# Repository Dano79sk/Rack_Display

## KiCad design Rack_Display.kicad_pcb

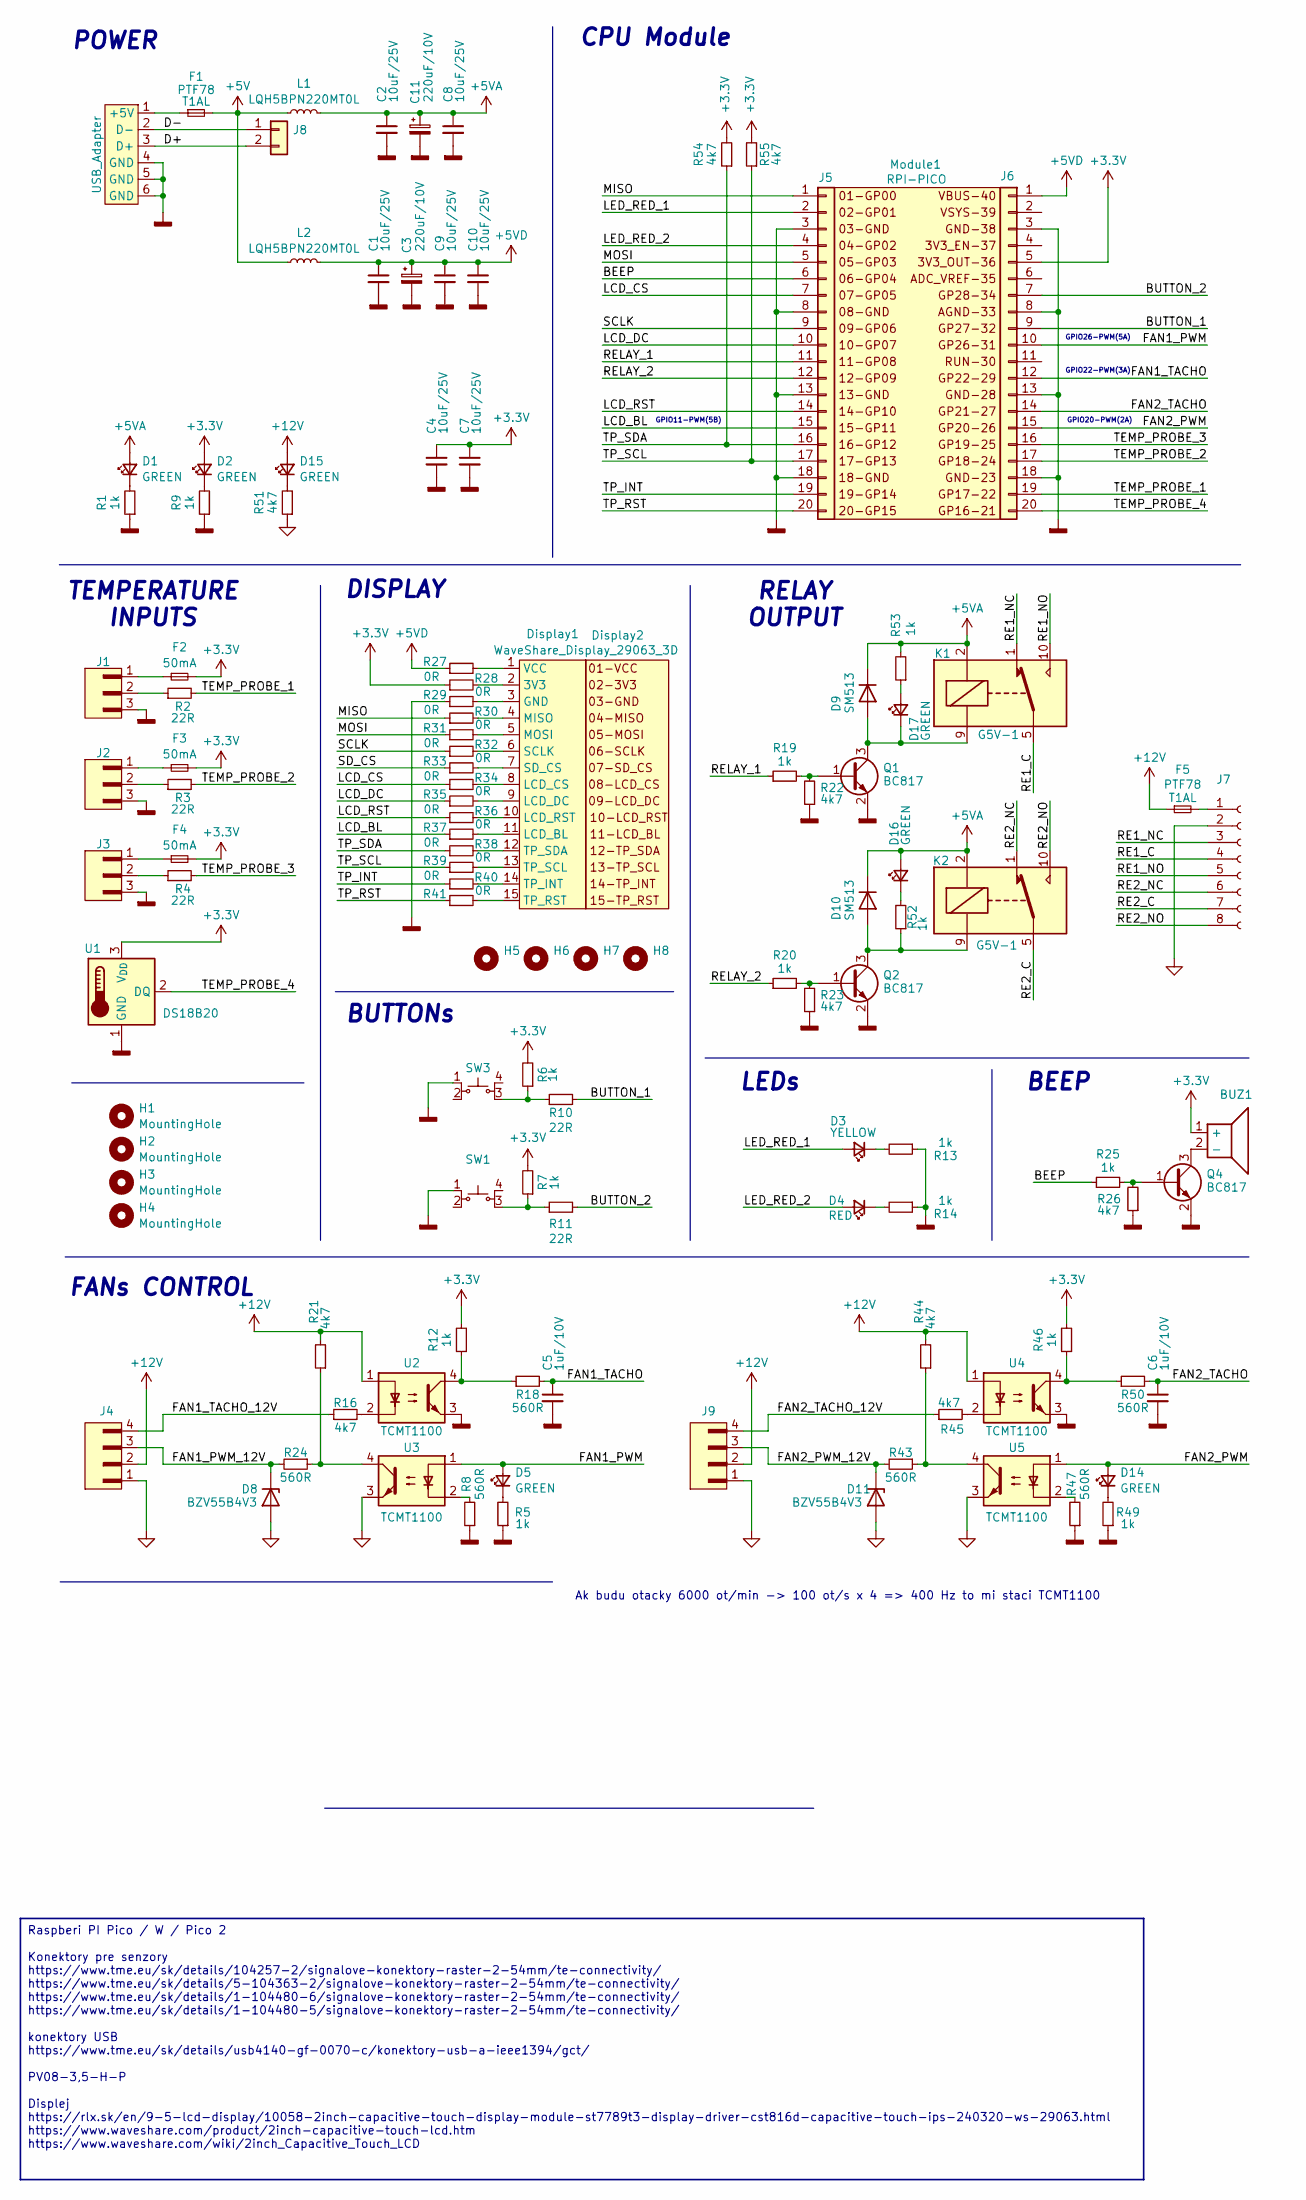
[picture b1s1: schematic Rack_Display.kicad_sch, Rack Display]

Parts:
BUZ1: LEB9055B-05B-2.7
C1, C4, C7, C9, C10: 10uF/25V; C_1206_3216Metric
C2, C8: 10uF/25V; C_0603_1608Metric
C3, C11: 220uF/10V; CP_Radial_D6.3mm_P2.50mm
C5, C6: 1uF/10V; C_0603_1608Metric
D1, D2, D5, D14, D15: GREEN; LED_0603_1608Metric
D3: YELLOW; LED_D3.0mm_Clear
D4: RED; LED_D3.0mm_Clear
D8, D11: BZV55B4V3; D_MiniMELF
D9, D10: SM513; D_MELF
D16, D17: GREEN; LED_D3.0mm_Clear
Display1: WaveShare_Display_29063; PinHeader_1x15_P2.54mm_Horizontal
Display2: WaveShare_Display_29063_3D; WaveShare_Display_29063
F1, F5: PTF78; Fuseholder_Cylinder-5x20mm_Stelvio-Kontek_PTF78_Horizontal_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
F2, F3, F4: 50mA; Fuse_1206_3216Metric
H1, H2, H3, H4: MountingHole; MountingHole_2.7mm
H5, H6, H7, H8: MountingHole; MountingHole_2.2mm_M2
J1, J2, J3: 5-104363-2
J4, J9: 5-104362-3
J5, J6: Conn_01x20; PinSocket_1x20_P2.54mm_Vertical
J7: Conn_01x08_Socket; PhoenixContact_MC_1,5_8-G-3.5_1x08_P3.50mm_Horizontal
J8: Conn_01x02; Molex_KK-254_AE-6410-02A_1x02_P2.54mm_Vertical
K1, K2: G5V-1; Relay_SPDT_Omron_G5V-1
L1, L2: LQH5BPN220MT0L; L_Taiyo-Yuden_MD-5050
Module1: RPI-PICO; R_Pi_Pico_Module
Module2: USB_Adapter
Q1, Q2, Q4: BC817; SOT-23
R1, R5, R6, R7, R9, R12, R13, R14, R19, R20, R25, R46, R49, R52, R53: 1k; R_0603_1608Metric
R2, R3, R4, R10, R11: 22R; R_0603_1608Metric
R8, R18, R24, R43, R47, R50: 560R; R_0603_1608Metric
R16, R21, R22, R23, R26, R44, R45, R51, R54, R55: 4k7; R_0603_1608Metric
R27, R28, R29, R30, R31, R32, R33, R34, R35, R36, R37, R38, R39, R40, R41: 0R; R_0603_1608Metric
SW1, SW3: 1437565-5
U1: DS18B20; TO-92_Inline
U2, U3, U4, U5: TCMT1100; SOP-4_4.4x2.6mm_P1.27mm

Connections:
+3.3V: BUZ1.1 (+), C4.1, C7.1, D2.2 (A), F2.2, F3.2, F4.2, J6.5, R6.2, R7.2, R12.2, R28.1, R46.2, R54.2, R55.2, U1.3 (V_{DD})
+5V: F1.2, L1.1, L2.1
+5VA: C2.1, C8.1, C11.1, D1.2 (A), D9.1 (K), D10.1 (K), D16.2 (A), K1.2, K2.2, L1.2, R53.2
+5VD: C1.1, C3.1, C9.1, C10.1, J6.1, L2.2, R27.1
+12V: D15.2 (A), F5.1, J4.2, J9.2, R21.2, R44.2, U2.1, U4.1
/BEEP: J5.6, R25.1
/BUTTON_1: J6.9, R10.2
/BUTTON_2: J6.7, R11.2
/D+: J8.2, Module2.3 (D+)
/D-: J8.1, Module2.2 (D-)
/FAN1_PWM: D5.2 (A), J6.10, U3.1
/FAN1_PWM_12V: D8.1 (K), J4.3, R24.2
/FAN1_TACHO: C5.1, J6.12, R18.2
/FAN1_TACHO_12V: J4.4, R16.1
/FAN2_PWM: D14.2 (A), J6.15, U5.1
/FAN2_PWM_12V: D11.1 (K), J9.3, R43.2
/FAN2_TACHO: C6.1, J6.14, R50.2
/FAN2_TACHO_12V: J9.4, R45.1
/LCD_BL: J5.15, R37.1
/LCD_CS: J5.7, R34.1
/LCD_DC: J5.10, R35.1
/LCD_RST: J5.14, R36.1
/LED_RED_1: D3.2 (A), J5.2
/LED_RED_2: D4.2 (A), J5.4
/MISO: J5.1, R30.1
/MOSI: J5.5, R31.1
/RE1_C: J7.4, K1.5, K1.6
/RE1_NC: J7.3, K1.1
/RE1_NO: J7.5, K1.10
/RE2_C: J7.7, K2.5, K2.6
/RE2_NC: J7.6, K2.1
/RE2_NO: J7.8, K2.10
/RELAY_1: J5.11, R19.1
/RELAY_2: J5.12, R20.1
/SCLK: J5.9, R32.1
/SD_CS: R33.1
/TEMP_PROBE_1: J6.19, R2.2
/TEMP_PROBE_2: J6.17, R3.2
/TEMP_PROBE_3: J6.16, R4.2
/TEMP_PROBE_4: J6.20, U1.2 (DQ)
/TP_INT: J5.19, R40.1
/TP_RST: J5.20, R41.1
/TP_SCL: J5.17, R39.1, R55.1
/TP_SDA: J5.16, R38.1, R54.1
GNDD: C1.2, C2.2, C3.2, C4.2, C5.2, C6.2, C7.2, C8.2, C9.2, C10.2, C11.2, J1.3, J2.3, J3.3, J5.3, J5.8, J5.13, J5.18, J6.3, J6.8, J6.13, J6.18, Module2.4 (GND), Module2.5 (GND), Module2.6 (GND), Q1.2 (E), Q2.2 (E), Q4.2 (E), R1.1, R5.1, R8.1, R9.1, R13.1, R14.1, R22.1, R23.1, R26.1, R29.1, R47.1, R49.1, SW1.1, SW3.1, U1.1 (GND), U2.3, U4.3
GNDS: D8.2 (A), D11.2 (A), J4.1, J7.2, J9.1, R51.1, U3.3, U5.3
unnamed: BUZ1.2 (-), Q4.3 (C)
unnamed: D1.1 (K), R1.2
unnamed: D2.1 (K), R9.2
unnamed: D3.1 (K), R13.2
unnamed: D4.1 (K), R14.2
unnamed: D5.1 (K), R5.2
unnamed: D10.2 (A), K2.9, Q2.3 (C), R52.1
unnamed: D14.1 (K), R49.2
unnamed: D15.1 (K), R51.2
unnamed: D16.1 (K), R52.2
unnamed: D17.2 (A), R53.1
unnamed: D9.2 (A), D17.1 (K), K1.9, Q1.3 (C)
unnamed: Display1.2 (3V3), R28.2
unnamed: Display1.3 (GND), R29.2
unnamed: Display1.11 (LCD_BL), R37.2
unnamed: Display1.8 (LCD_CS), R34.2
unnamed: Display1.9 (LCD_DC), R35.2
unnamed: Display1.10 (LCD_RST), R36.2
unnamed: Display1.4 (MISO), R30.2
unnamed: Display1.5 (MOSI), R31.2
unnamed: Display1.6 (SCLK), R32.2
unnamed: Display1.7 (SD_CS), R33.2
unnamed: Display1.14 (TP_INT), R40.2
unnamed: Display1.15 (TP_RST), R41.2
unnamed: Display1.13 (TP_SCL), R39.2
unnamed: Display1.12 (TP_SDA), R38.2
unnamed: Display1.1 (VCC), R27.2
unnamed: F2.1, J1.1
unnamed: F3.1, J2.1
unnamed: F4.1, J3.1
unnamed: J1.2, R2.1
unnamed: J2.2, R3.1
unnamed: J3.2, R4.1
unnamed: F5.2, J7.1
unnamed: F1.1, Module2.1 (+5V)
unnamed: Q1.1 (B), R19.2, R22.2
unnamed: Q2.1 (B), R20.2, R23.2
unnamed: Q4.1 (B), R25.2, R26.2
unnamed: R8.2, U3.2
unnamed: R6.1, R10.1, SW3.3
unnamed: R7.1, R11.1, SW1.3
unnamed: R12.1, R18.1, U2.4
unnamed: R16.2, U2.2
unnamed: R21.1, R24.1, U3.4
unnamed: R43.1, R44.1, U5.4
unnamed: R45.2, U4.2
unnamed: R46.1, R50.1, U4.4
unnamed: R47.2, U5.2

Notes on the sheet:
Raspberi PI Pico / W / Pico 2 Konektory pre senzory https://www.tme.eu/sk/details/104257-2/signalove-konektory-raster-2-54mm/te-connectivity/ https://www.tme.eu/sk/details/5-104363-2/signalove-konektory-raster-2-54mm/te-connectivity/ https://www.tme.eu/sk/details/1-104480-6/signalove-konektory-rast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
FANs CONTROL
CPU Module
BEEP
GPIO22-PWM(3A)
DISPLAY
GPIO26-PWM(5A)
LEDs
GPIO20-PWM(2A)
POWER
Ak budu otacky 6000 ot/min -> 100 ot/s x 4 => 400 Hz to mi staci TCMT1100
TEMPERATURE INPUTS
GPIO11-PWM(5B)
BUTTONs
RELAY OUTPUT

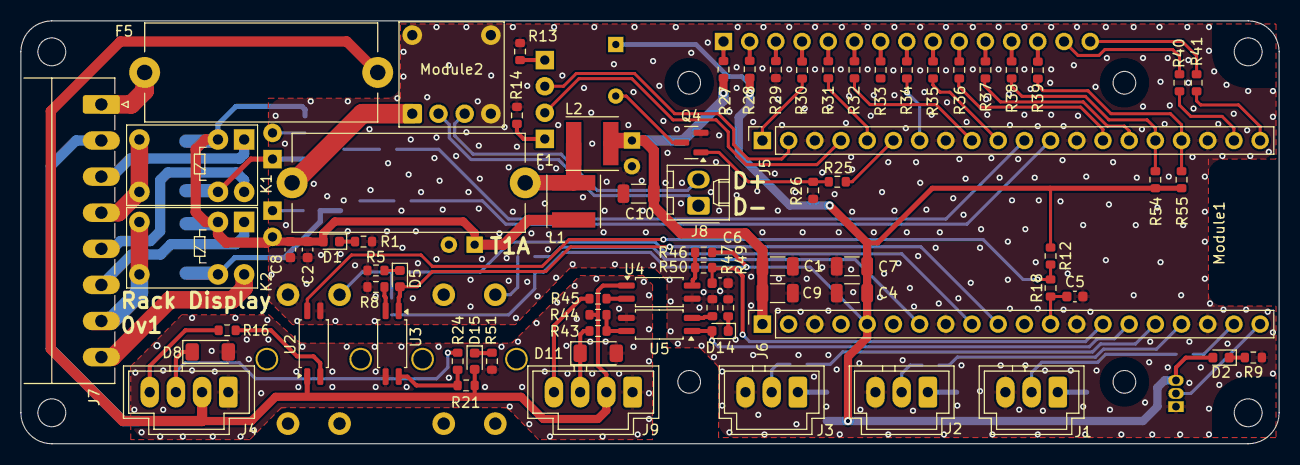
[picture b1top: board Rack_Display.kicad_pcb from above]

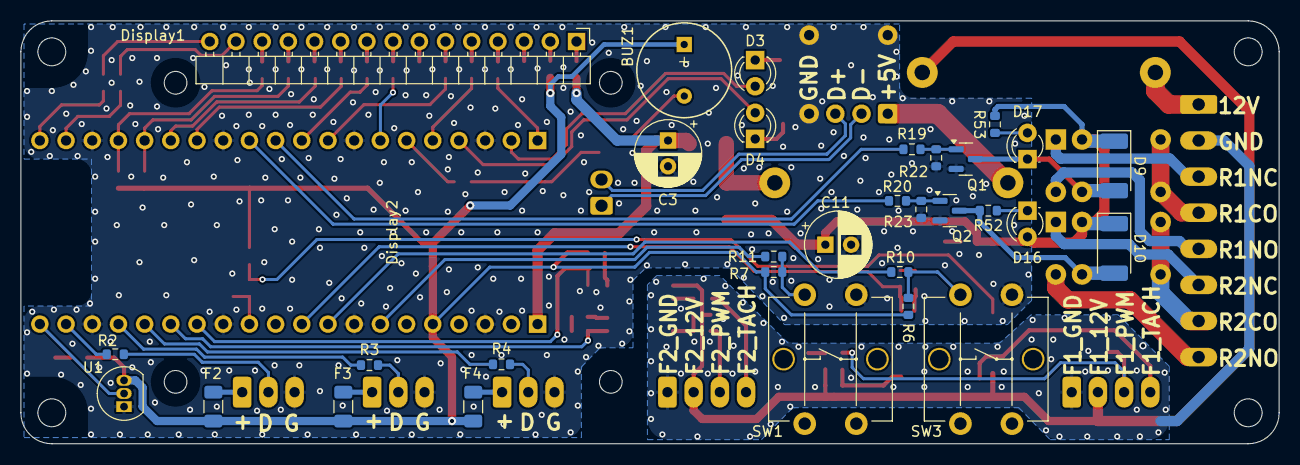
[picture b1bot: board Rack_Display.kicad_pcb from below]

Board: 2 copper layers, 122.0 x 41.0 mm, 116 parts (32 on the bottom side), 93 nets.

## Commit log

2024-12-16 test
2024-12-16 test2
2024-12-16 "TME"
